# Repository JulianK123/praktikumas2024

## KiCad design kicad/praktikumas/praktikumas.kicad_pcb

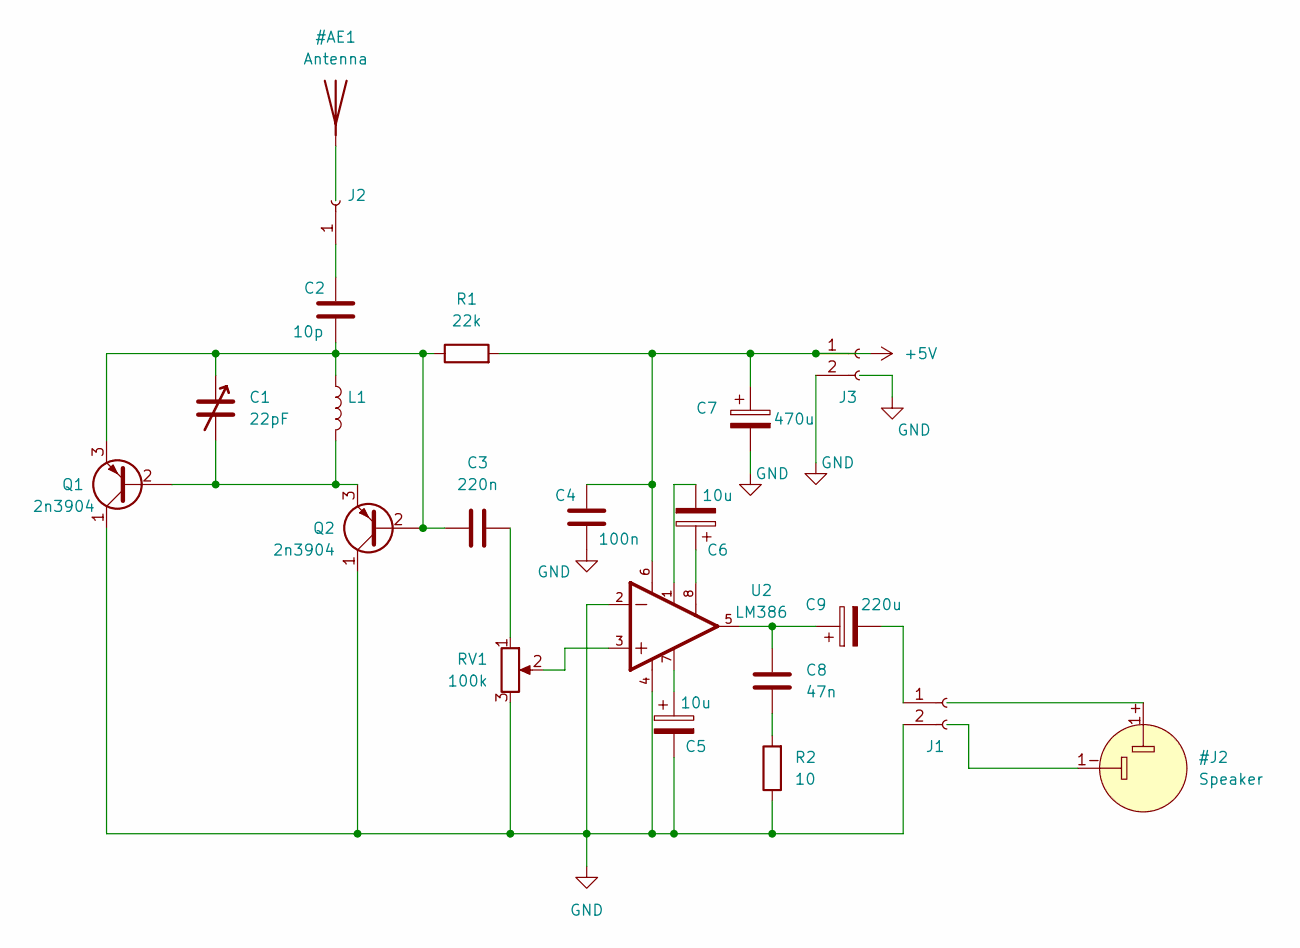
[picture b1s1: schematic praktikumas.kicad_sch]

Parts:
C1: 22pF; CP_Radial_D6.3mm_P2.50mm
C2: 10p; C_Disc_D5.1mm_W3.2mm_P5.00mm
C3: 220n; C_Disc_D5.1mm_W3.2mm_P5.00mm
C4: 100n; C_Disc_D5.1mm_W3.2mm_P5.00mm
C5, C6: 10u; CP_Radial_D6.3mm_P2.50mm
C7: 470u; CP_Radial_D10.0mm_P2.50mm
C8: 47n; C_Disc_D5.1mm_W3.2mm_P5.00mm
C9: 220u; CP_Radial_D8.0mm_P2.50mm
J1, J3: sp; PinSocket_1x02_P2.54mm_Horizontal
J2: Conn_01x01_Socket; PinSocket_1x01_P2.54mm_Horizontal
L1: L_Axial_L5.3mm_D2.2mm_P7.62mm_Horizontal_Vishay_IM-1
Q1, Q2: 2n3904; TO-92L_Inline
R1: 22k; R_Axial_DIN0207_L6.3mm_D2.5mm_P10.16mm_Horizontal
R2: 10; R_Axial_DIN0207_L6.3mm_D2.5mm_P10.16mm_Horizontal
RV1: 100k; Potentiometer_Bourns_3266Y_Vertical
U2: LM386; DIP08

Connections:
+5V: C4.2, C7.1, J3.1, R1.2, U2.6
GND: C4.1, C5.2, C7.2, J1.2, J3.2, Q1.1 (C), Q2.1 (C), R2.1, RV1.3, U2.2, U2.4
unnamed: C3.2, RV1.1
unnamed: C5.1, U2.7
unnamed: C6.1, U2.8
unnamed: C6.2, U2.1
unnamed: C8.1, R2.2
unnamed: C8.2, C9.1, U2.5
unnamed: C9.2, J1.1
unnamed: C2.2, J2.1
unnamed: C1.2, L1.2, Q1.2 (B), Q2.3 (E)
unnamed: C1.1, C2.1, C3.1, L1.1, Q1.3 (E), Q2.2 (B), R1.1
unnamed: RV1.2, U2.3

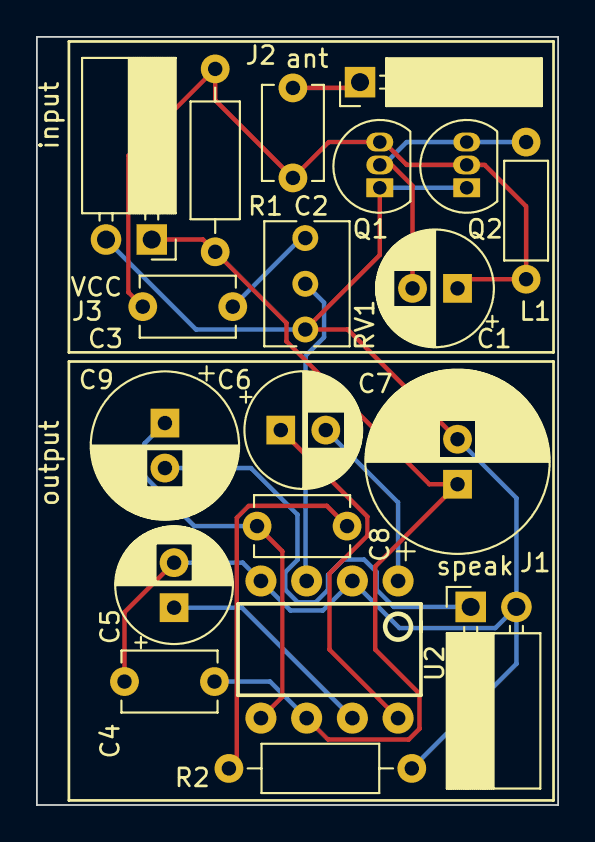
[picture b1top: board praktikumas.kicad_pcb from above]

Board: 2 copper layers, 29.0 x 42.7 mm, 19 parts (0 on the bottom side), 13 nets.
